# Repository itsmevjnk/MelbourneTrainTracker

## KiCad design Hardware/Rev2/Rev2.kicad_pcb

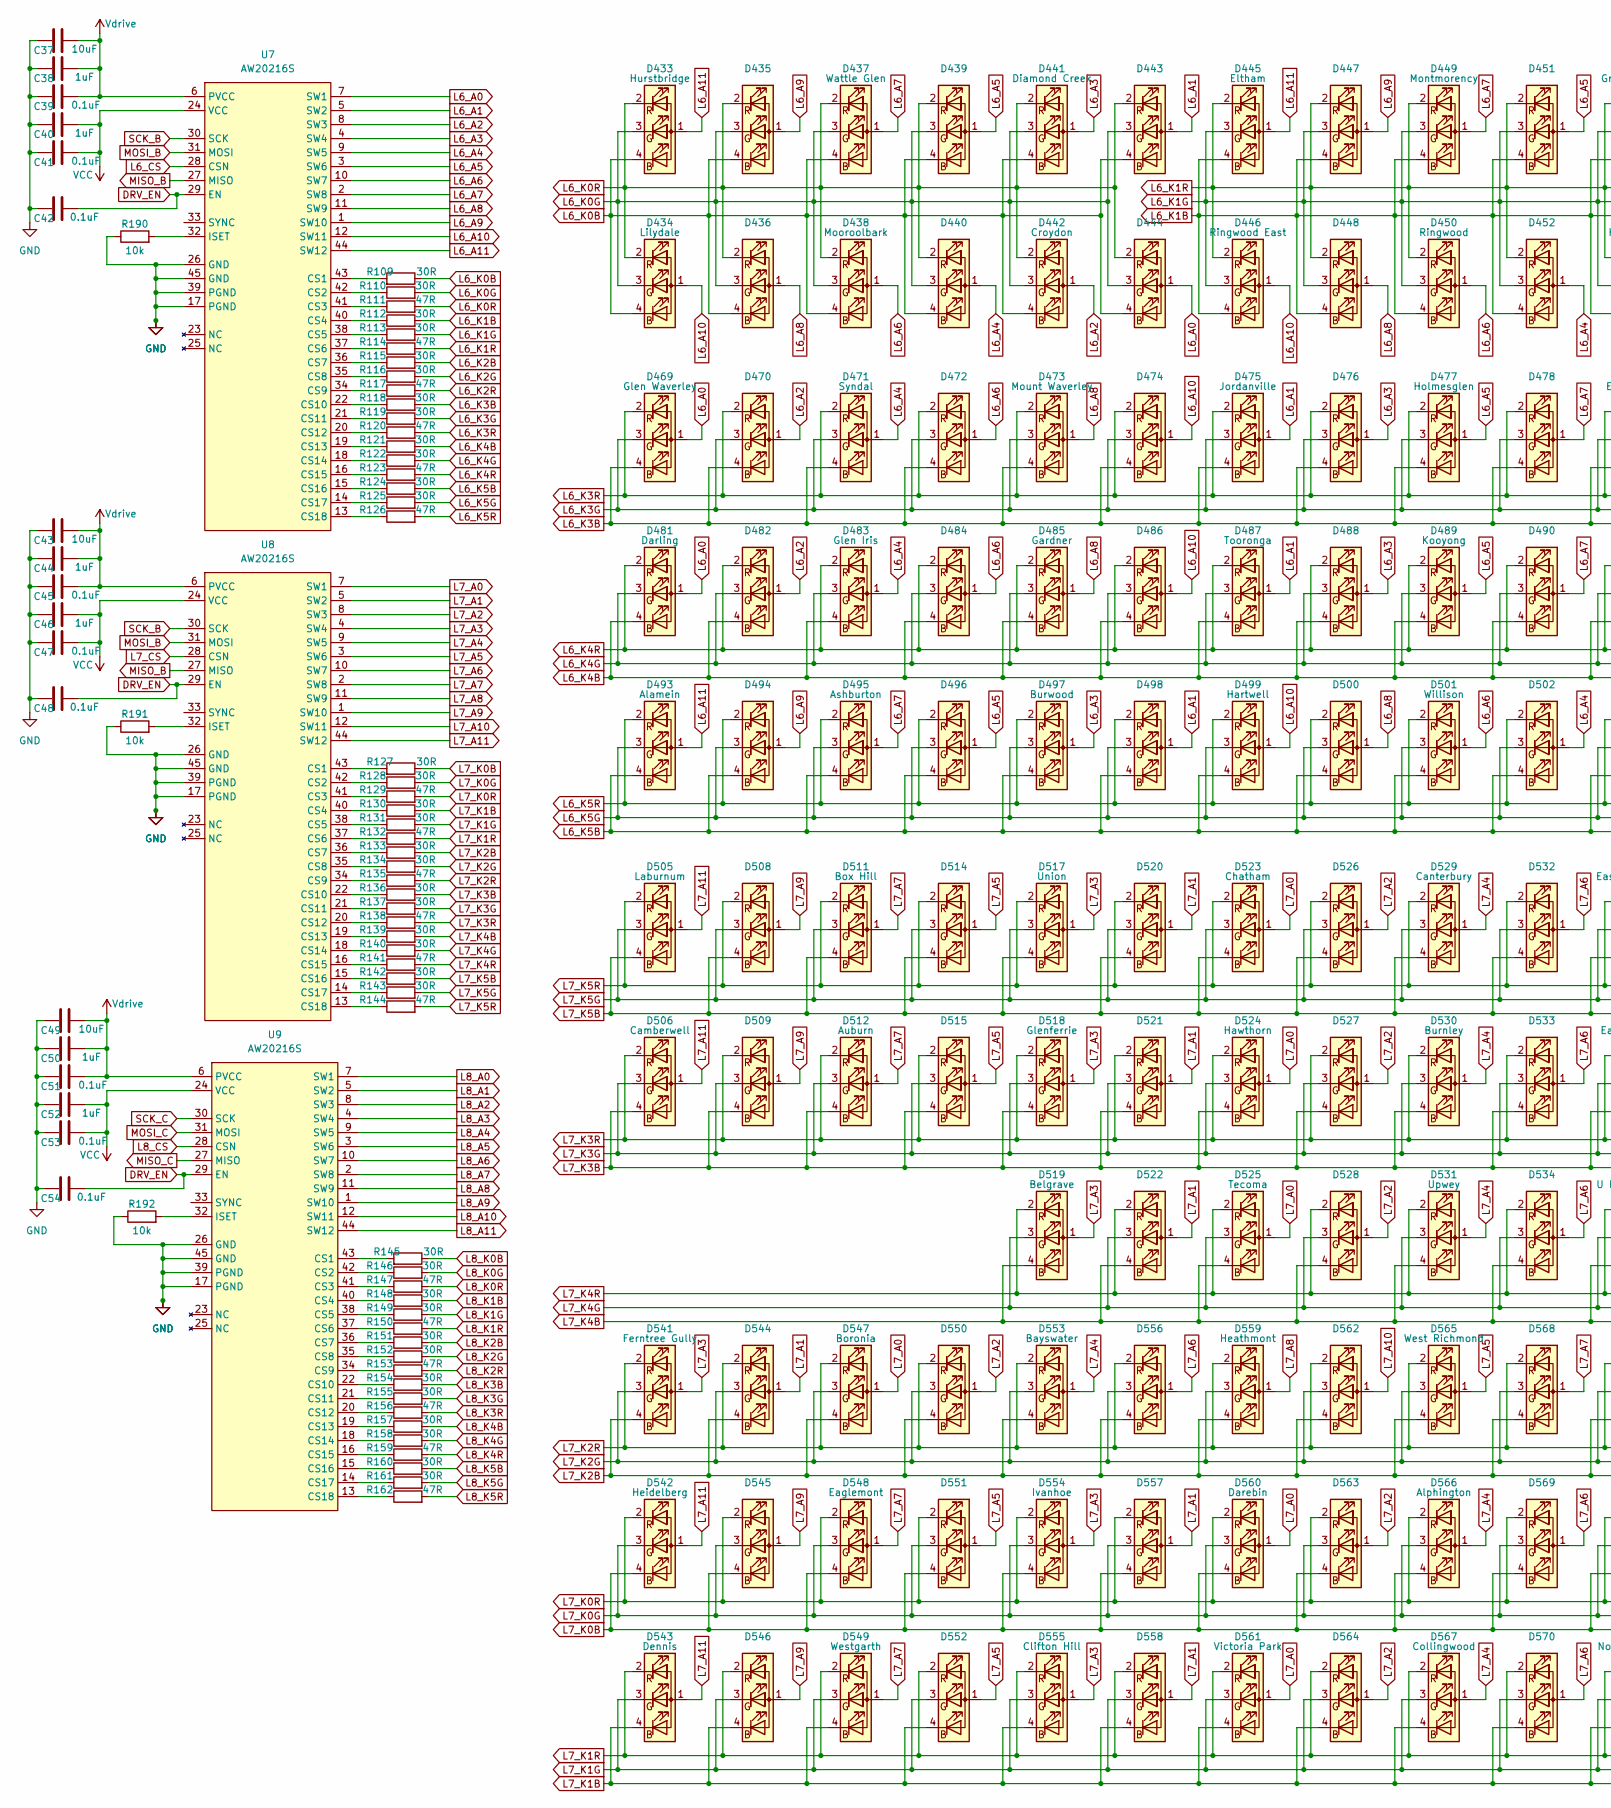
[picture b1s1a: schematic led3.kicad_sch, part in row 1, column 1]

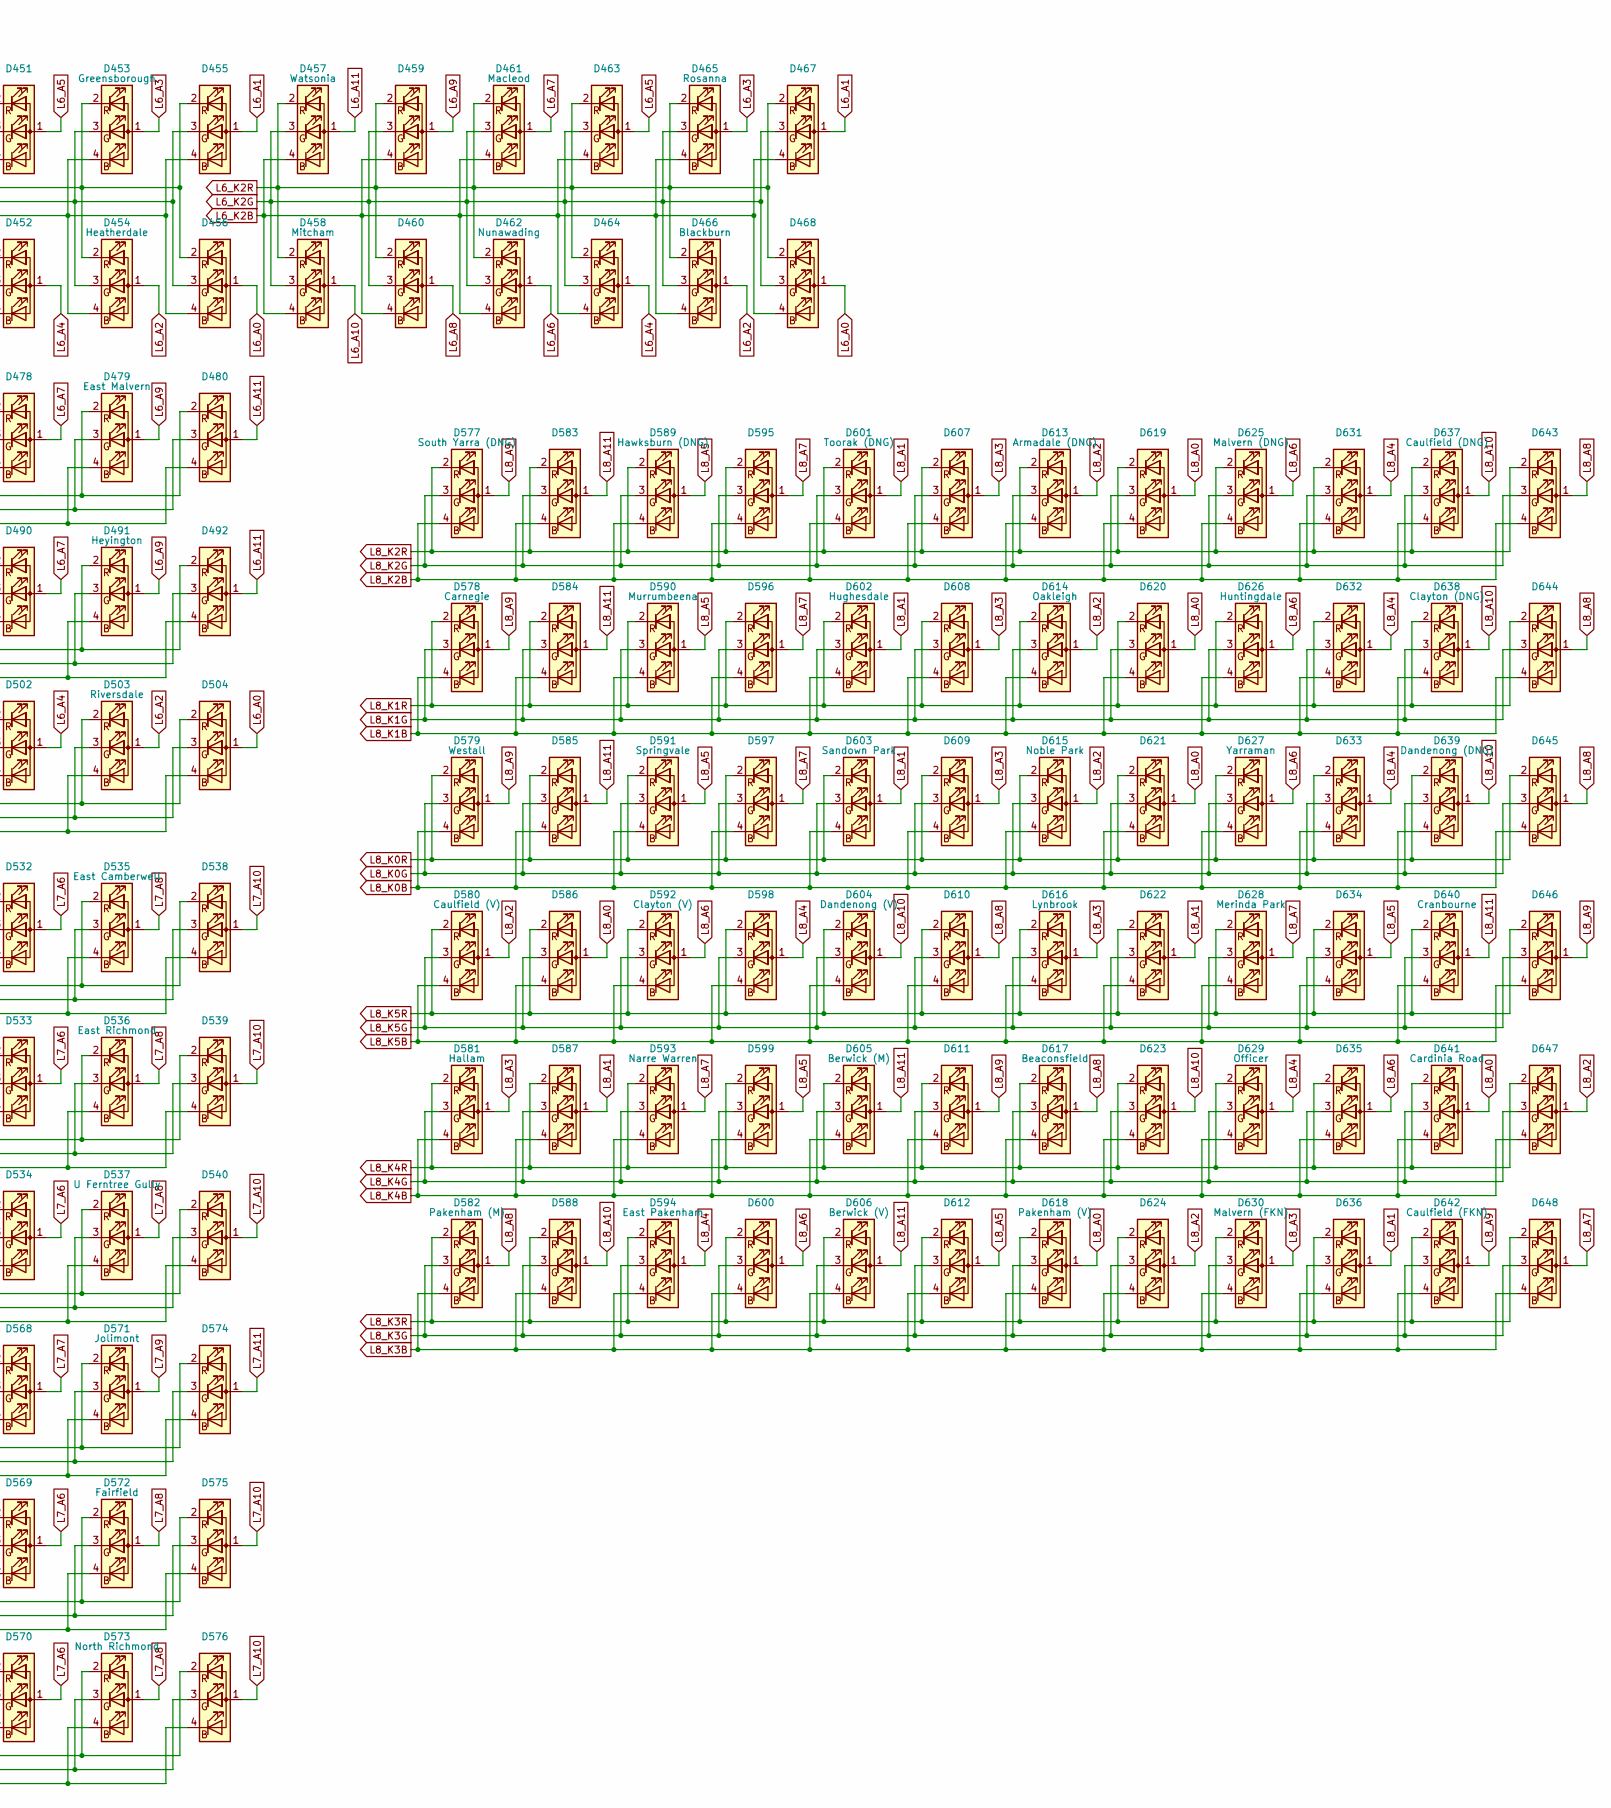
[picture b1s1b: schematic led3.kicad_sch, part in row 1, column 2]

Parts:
C37, C43, C49: 10uF; C_0805_2012Metric_Pad1.18x1.45mm_HandSolder; MPN C380332
C38, C40, C44, C46, C50, C52: 1uF; C_0603_1608Metric_Pad1.08x0.95mm_HandSolder; MPN C6119849
C39, C41, C42, C45, C47, C48, C51, C53, C54: 0.1uF; C_0603_1608Metric_Pad1.08x0.95mm_HandSolder; MPN C14663
D433, D434, D435, D436, D437, D438, D439, D440, D441, D442, D443, D444, D445, D446, D447, D448, D449, D450, D451, D452, D453, D454, D455, D456, D457, D458, D459, D460, D461, D462, D463, D464, D465, D466, D467, D468, D469, D470, D471, D472, D473, D474, D475, D476, D477, D478, D479, D480, D481, D482, D483, D484, D485, D486, D487, D488, D489, D490, D491, D492, D493, D494, D495, D496, D497, D498, D499, D500, D501, D502, D503, D504, D505, D506, D508, D509, D511, D512, D514, D515, D517, D518, D519, D520, D521, D522, D523, D524, D525, D526, D527, D528, D529, D530, D531, D532, D533, D534, D535, D536, D537, D538, D539, D540, D541, D542, D543, D544, D545, D546, D547, D548, D549, D550, D551, D552, D553, D554, D555, D556, D557, D558, D559, D560, D561, D562, D563, D564, D565, D566, D567, D568, D569, D570, D571, D572, D573, D574, D575, D576, D577, D578, D579, D580, D581, D582, D583, D584, D585, D586, D587, D588, D589, D590, D591, D592, D593, D594, D595, D596, D597, D598, D599, D600, D601, D602, D603, D604, D605, D606, D607, D608, D609, D610, D611, D612, D613, D614, D615, D616, D617, D618, D619, D620, D621, D622, D623, D624, D625, D626, D627, D628, D629, D630, D631, D632, D633, D634, D635, D636, D637, D638, D639, D640, D641, D642, D643, D644, D645, D646, D647, D648: XL-B1010RGBT-HF; LED_RGB_Xinglight-1010; MPN C22464515
R109, R110, R112, R113, R115, R116, R118, R119, R121, R122, R124, R125, R127, R128, R130, R131, R133, R134, R136, R137, R139, R140, R142, R143, R145, R146, R148, R149, R151, R152, R154, R155, R157, R158, R160, R161: 30R; R_0805_2012Metric_Pad1.20x1.40mm_HandSolder
R111, R114, R117, R120, R123, R126, R129, R132, R135, R138, R141, R144, R147, R150, R153, R156, R159, R162: 47R; R_0805_2012Metric_Pad1.20x1.40mm_HandSolder
R190, R191, R192: 10k; R_0603_1608Metric_Pad0.98x0.95mm_HandSolder; MPN C15401
U7, U8, U9: AW20216S; QFN-44-1EP_5x5mm_P0.4mm_EP2.45x2.45mm; MPN C7385556

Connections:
+3.3V: C40.2, C41.2, C46.2, C47.2, C52.2, C53.2, U7.24 (VCC), U8.24 (VCC), U9.24 (VCC); also elsewhere on the board
+5V: C37.2, C38.2, C39.2, C43.2, C44.2, C45.2, C49.2, C50.2, C51.2, U7.6 (PVCC), U8.6 (PVCC), U9.6 (PVCC); also elsewhere on the board
DRV_EN: C42.2, C48.2, C54.2, U7.29 (EN), U8.29 (EN), U9.29 (EN); also elsewhere on the board
GND: C37.1, C38.1, C39.1, C40.1, C41.1, C42.1, C43.1, C44.1, C45.1, C46.1, C47.1, C48.1, C49.1, C50.1, C51.1, C52.1, C53.1, C54.1, R190.1, R191.1, R192.1, U7.17 (PGND), U7.26 (GND), U7.39 (PGND), U7.45 (GND), U8.17 (PGND), U8.26 (GND), U8.39 (PGND), U8.45 (GND), U9.17 (PGND), U9.26 (GND), U9.39 (PGND), U9.45 (GND); also elsewhere on the board
L6_A0: D444.1 (A), D456.1 (A), D468.1 (A), D469.1 (A), D481.1 (A), D504.1 (A), U7.7 (SW1)
L6_A1: D443.1 (A), D455.1 (A), D467.1 (A), D475.1 (A), D487.1 (A), D498.1 (A), U7.5 (SW2)
L6_A2: D442.1 (A), D454.1 (A), D466.1 (A), D470.1 (A), D482.1 (A), D503.1 (A), U7.8 (SW3)
L6_A3: D441.1 (A), D453.1 (A), D465.1 (A), D476.1 (A), D488.1 (A), D497.1 (A), U7.4 (SW4)
L6_A4: D440.1 (A), D452.1 (A), D464.1 (A), D471.1 (A), D483.1 (A), D502.1 (A), U7.9 (SW5)
L6_A5: D439.1 (A), D451.1 (A), D463.1 (A), D477.1 (A), D489.1 (A), D496.1 (A), U7.3 (SW6)
L6_A6: D438.1 (A), D450.1 (A), D462.1 (A), D472.1 (A), D484.1 (A), D501.1 (A), U7.10 (SW7)
L6_A7: D437.1 (A), D449.1 (A), D461.1 (A), D478.1 (A), D490.1 (A), D495.1 (A), U7.2 (SW8)
L6_A8: D436.1 (A), D448.1 (A), D460.1 (A), D473.1 (A), D485.1 (A), D500.1 (A), U7.11 (SW9)
L6_A9: D435.1 (A), D447.1 (A), D459.1 (A), D479.1 (A), D491.1 (A), D494.1 (A), U7.1 (SW10)
L6_A10: D434.1 (A), D446.1 (A), D458.1 (A), D474.1 (A), D486.1 (A), D499.1 (A), U7.12 (SW11)
L6_A11: D433.1 (A), D445.1 (A), D457.1 (A), D480.1 (A), D492.1 (A), D493.1 (A), U7.44 (SW12)
L6_CS: U7.28 (CSN); also elsewhere on the board
L6_K0B: D433.4 (BK), D434.4 (BK), D435.4 (BK), D436.4 (BK), D437.4 (BK), D438.4 (BK), D439.4 (BK), D440.4 (BK), D441.4 (BK), D442.4 (BK), D443.4 (BK), D444.4 (BK), R109.1
L6_K0G: D433.3 (GK), D434.3 (GK), D435.3 (GK), D436.3 (GK), D437.3 (GK), D438.3 (GK), D439.3 (GK), D440.3 (GK), D441.3 (GK), D442.3 (GK), D443.3 (GK), D444.3 (GK), R110.2
L6_K0R: D433.2 (RK), D434.2 (RK), D435.2 (RK), D436.2 (RK), D437.2 (RK), D438.2 (RK), D439.2 (RK), D440.2 (RK), D441.2 (RK), D442.2 (RK), D443.2 (RK), D444.2 (RK), R111.2
L6_K1B: D445.4 (BK), D446.4 (BK), D447.4 (BK), D448.4 (BK), D449.4 (BK), D450.4 (BK), D451.4 (BK), D452.4 (BK), D453.4 (BK), D454.4 (BK), D455.4 (BK), D456.4 (BK), R112.2
L6_K1G: D445.3 (GK), D446.3 (GK), D447.3 (GK), D448.3 (GK), D449.3 (GK), D450.3 (GK), D451.3 (GK), D452.3 (GK), D453.3 (GK), D454.3 (GK), D455.3 (GK), D456.3 (GK), R113.2
L6_K1R: D445.2 (RK), D446.2 (RK), D447.2 (RK), D448.2 (RK), D449.2 (RK), D450.2 (RK), D451.2 (RK), D452.2 (RK), D453.2 (RK), D454.2 (RK), D455.2 (RK), D456.2 (RK), R114.2
L6_K2B: D457.4 (BK), D458.4 (BK), D459.4 (BK), D460.4 (BK), D461.4 (BK), D462.4 (BK), D463.4 (BK), D464.4 (BK), D465.4 (BK), D466.4 (BK), D467.4 (BK), D468.4 (BK), R115.2
L6_K2G: D457.3 (GK), D458.3 (GK), D459.3 (GK), D460.3 (GK), D461.3 (GK), D462.3 (GK), D463.3 (GK), D464.3 (GK), D465.3 (GK), D466.3 (GK), D467.3 (GK), D468.3 (GK), R116.2
L6_K2R: D457.2 (RK), D458.2 (RK), D459.2 (RK), D460.2 (RK), D461.2 (RK), D462.2 (RK), D463.2 (RK), D464.2 (RK), D465.2 (RK), D466.2 (RK), D467.2 (RK), D468.2 (RK), R117.2
L6_K3B: D469.4 (BK), D470.4 (BK), D471.4 (BK), D472.4 (BK), D473.4 (BK), D474.4 (BK), D475.4 (BK), D476.4 (BK), D477.4 (BK), D478.4 (BK), D479.4 (BK), D480.4 (BK), R118.2
L6_K3G: D469.3 (GK), D470.3 (GK), D471.3 (GK), D472.3 (GK), D473.3 (GK), D474.3 (GK), D475.3 (GK), D476.3 (GK), D477.3 (GK), D478.3 (GK), D479.3 (GK), D480.3 (GK), R119.2
L6_K3R: D469.2 (RK), D470.2 (RK), D471.2 (RK), D472.2 (RK), D473.2 (RK), D474.2 (RK), D475.2 (RK), D476.2 (RK), D477.2 (RK), D478.2 (RK), D479.2 (RK), D480.2 (RK), R120.2
L6_K4B: D481.4 (BK), D482.4 (BK), D483.4 (BK), D484.4 (BK), D485.4 (BK), D486.4 (BK), D487.4 (BK), D488.4 (BK), D489.4 (BK), D490.4 (BK), D491.4 (BK), D492.4 (BK), R121.2
L6_K4G: D481.3 (GK), D482.3 (GK), D483.3 (GK), D484.3 (GK), D485.3 (GK), D486.3 (GK), D487.3 (GK), D488.3 (GK), D489.3 (GK), D490.3 (GK), D491.3 (GK), D492.3 (GK), R122.2
L6_K4R: D481.2 (RK), D482.2 (RK), D483.2 (RK), D484.2 (RK), D485.2 (RK), D486.2 (RK), D487.2 (RK), D488.2 (RK), D489.2 (RK), D490.2 (RK), D491.2 (RK), D492.2 (RK), R123.2
L6_K5B: D493.4 (BK), D494.4 (BK), D495.4 (BK), D496.4 (BK), D497.4 (BK), D498.4 (BK), D499.4 (BK), D500.4 (BK), D501.4 (BK), D502.4 (BK), D503.4 (BK), D504.4 (BK), R124.2
L6_K5G: D493.3 (GK), D494.3 (GK), D495.3 (GK), D496.3 (GK), D497.3 (GK), D498.3 (GK), D499.3 (GK), D500.3 (GK), D501.3 (GK), D502.3 (GK), D503.3 (GK), D504.3 (GK), R125.2
L6_K5R: D493.2 (RK), D494.2 (RK), D495.2 (RK), D496.2 (RK), D497.2 (RK), D498.2 (RK), D499.2 (RK), D500.2 (RK), D501.2 (RK), D502.2 (RK), D503.2 (RK), D504.2 (RK), R126.2
L7_A0: D523.1 (A), D524.1 (A), D525.1 (A), D547.1 (A), D560.1 (A), D561.1 (A), U8.7 (SW1)
L7_A1: D520.1 (A), D521.1 (A), D522.1 (A), D544.1 (A), D557.1 (A), D558.1 (A), U8.5 (SW2)
L7_A2: D526.1 (A), D527.1 (A), D528.1 (A), D550.1 (A), D563.1 (A), D564.1 (A), U8.8 (SW3)
L7_A3: D517.1 (A), D518.1 (A), D519.1 (A), D541.1 (A), D554.1 (A), D555.1 (A), U8.4 (SW4)
L7_A4: D529.1 (A), D530.1 (A), D531.1 (A), D553.1 (A), D566.1 (A), D567.1 (A), U8.9 (SW5)
L7_A5: D514.1 (A), D515.1 (A), D551.1 (A), D552.1 (A), D565.1 (A), U8.3 (SW6)
L7_A6: D532.1 (A), D533.1 (A), D534.1 (A), D556.1 (A), D569.1 (A), D570.1 (A), U8.10 (SW7)
L7_A7: D511.1 (A), D512.1 (A), D548.1 (A), D549.1 (A), D568.1 (A), U8.2 (SW8)
L7_A8: D535.1 (A), D536.1 (A), D537.1 (A), D559.1 (A), D572.1 (A), D573.1 (A), U8.11 (SW9)
L7_A9: D508.1 (A), D509.1 (A), D545.1 (A), D546.1 (A), D571.1 (A), U8.1 (SW10)
L7_A10: D538.1 (A), D539.1 (A), D540.1 (A), D562.1 (A), D575.1 (A), D576.1 (A), U8.12 (SW11)
L7_A11: D505.1 (A), D506.1 (A), D542.1 (A), D543.1 (A), D574.1 (A), U8.44 (SW12)
L7_CS: U8.28 (CSN); also elsewhere on the board
L7_K0B: D542.4 (BK), D545.4 (BK), D548.4 (BK), D551.4 (BK), D554.4 (BK), D557.4 (BK), D560.4 (BK), D563.4 (BK), D566.4 (BK), D569.4 (BK), D572.4 (BK), D575.4 (BK), R127.1
L7_K0G: D542.3 (GK), D545.3 (GK), D548.3 (GK), D551.3 (GK), D554.3 (GK), D557.3 (GK), D560.3 (GK), D563.3 (GK), D566.3 (GK), D569.3 (GK), D572.3 (GK), D575.3 (GK), R128.2
L7_K0R: D542.2 (RK), D545.2 (RK), D548.2 (RK), D551.2 (RK), D554.2 (RK), D557.2 (RK), D560.2 (RK), D563.2 (RK), D566.2 (RK), D569.2 (RK), D572.2 (RK), D575.2 (RK), R129.2
L7_K1B: D543.4 (BK), D546.4 (BK), D549.4 (BK), D552.4 (BK), D555.4 (BK), D558.4 (BK), D561.4 (BK), D564.4 (BK), D567.4 (BK), D570.4 (BK), D573.4 (BK), D576.4 (BK), R130.2
L7_K1G: D543.3 (GK), D546.3 (GK), D549.3 (GK), D552.3 (GK), D555.3 (GK), D558.3 (GK), D561.3 (GK), D564.3 (GK), D567.3 (GK), D570.3 (GK), D573.3 (GK), D576.3 (GK), R131.2
L7_K1R: D543.2 (RK), D546.2 (RK), D549.2 (RK), D552.2 (RK), D555.2 (RK), D558.2 (RK), D561.2 (RK), D564.2 (RK), D567.2 (RK), D570.2 (RK), D573.2 (RK), D576.2 (RK), R132.2
L7_K2B: D541.4 (BK), D544.4 (BK), D547.4 (BK), D550.4 (BK), D553.4 (BK), D556.4 (BK), D559.4 (BK), D562.4 (BK), D565.4 (BK), D568.4 (BK), D571.4 (BK), D574.4 (BK), R133.2
L7_K2G: D541.3 (GK), D544.3 (GK), D547.3 (GK), D550.3 (GK), D553.3 (GK), D556.3 (GK), D559.3 (GK), D562.3 (GK), D565.3 (GK), D568.3 (GK), D571.3 (GK), D574.3 (GK), R134.2
L7_K2R: D541.2 (RK), D544.2 (RK), D547.2 (RK), D550.2 (RK), D553.2 (RK), D556.2 (RK), D559.2 (RK), D562.2 (RK), D565.2 (RK), D568.2 (RK), D571.2 (RK), D574.2 (RK), R135.2
L7_K3B: D506.4 (BK), D509.4 (BK), D512.4 (BK), D515.4 (BK), D518.4 (BK), D521.4 (BK), D524.4 (BK), D527.4 (BK), D530.4 (BK), D533.4 (BK), D536.4 (BK), D539.4 (BK), R136.2
L7_K3G: D506.3 (GK), D509.3 (GK), D512.3 (GK), D515.3 (GK), D518.3 (GK), D521.3 (GK), D524.3 (GK), D527.3 (GK), D530.3 (GK), D533.3 (GK), D536.3 (GK), D539.3 (GK), R137.2
L7_K3R: D506.2 (RK), D509.2 (RK), D512.2 (RK), D515.2 (RK), D518.2 (RK), D521.2 (RK), D524.2 (RK), D527.2 (RK), D530.2 (RK), D533.2 (RK), D536.2 (RK), D539.2 (RK), R138.2
L7_K4B: D519.4 (BK), D522.4 (BK), D525.4 (BK), D528.4 (BK), D531.4 (BK), D534.4 (BK), D537.4 (BK), D540.4 (BK), R139.2
L7_K4G: D519.3 (GK), D522.3 (GK), D525.3 (GK), D528.3 (GK), D531.3 (GK), D534.3 (GK), D537.3 (GK), D540.3 (GK), R140.2
L7_K4R: D519.2 (RK), D522.2 (RK), D525.2 (RK), D528.2 (RK), D531.2 (RK), D534.2 (RK), D537.2 (RK), D540.2 (RK), R141.2
L7_K5B: D505.4 (BK), D508.4 (BK), D511.4 (BK), D514.4 (BK), D517.4 (BK), D520.4 (BK), D523.4 (BK), D526.4 (BK), D529.4 (BK), D532.4 (BK), D535.4 (BK), D538.4 (BK), R142.2
L7_K5G: D505.3 (GK), D508.3 (GK), D511.3 (GK), D514.3 (GK), D517.3 (GK), D520.3 (GK), D523.3 (GK), D526.3 (GK), D529.3 (GK), D532.3 (GK), D535.3 (GK), D538.3 (GK), R143.2
L7_K5R: D505.2 (RK), D508.2 (RK), D511.2 (RK), D514.2 (RK), D517.2 (RK), D520.2 (RK), D523.2 (RK), D526.2 (RK), D529.2 (RK), D532.2 (RK), D535.2 (RK), D538.2 (RK), R144.2
L8_A0: D586.1 (A), D618.1 (A), D619.1 (A), D620.1 (A), D621.1 (A), D641.1 (A), U9.7 (SW1)
L8_A1: D587.1 (A), D601.1 (A), D602.1 (A), D603.1 (A), D622.1 (A), D636.1 (A), U9.5 (SW2)
L8_A2: D580.1 (A), D613.1 (A), D614.1 (A), D615.1 (A), D624.1 (A), D647.1 (A), U9.8 (SW3)
L8_A3: D581.1 (A), D607.1 (A), D608.1 (A), D609.1 (A), D616.1 (A), D630.1 (A), U9.4 (SW4)
L8_A4: D594.1 (A), D598.1 (A), D629.1 (A), D631.1 (A), D632.1 (A), D633.1 (A), U9.9 (SW5)
L8_A5: D589.1 (A), D590.1 (A), D591.1 (A), D599.1 (A), D612.1 (A), D634.1 (A), U9.3 (SW6)
L8_A6: D592.1 (A), D600.1 (A), D625.1 (A), D626.1 (A), D627.1 (A), D635.1 (A), U9.10 (SW7)
L8_A7: D593.1 (A), D595.1 (A), D596.1 (A), D597.1 (A), D628.1 (A), D648.1 (A), U9.2 (SW8)
L8_A8: D582.1 (A), D610.1 (A), D617.1 (A), D643.1 (A), D644.1 (A), D645.1 (A), U9.11 (SW9)
L8_A9: D577.1 (A), D578.1 (A), D579.1 (A), D611.1 (A), D642.1 (A), D646.1 (A), U9.1 (SW10)
L8_A10: D588.1 (A), D604.1 (A), D623.1 (A), D637.1 (A), D638.1 (A), D639.1 (A), U9.12 (SW11)
L8_A11: D583.1 (A), D584.1 (A), D585.1 (A), D605.1 (A), D606.1 (A), D640.1 (A), U9.44 (SW12)
L8_CS: U9.28 (CSN); also elsewhere on the board
L8_K0B: D579.4 (BK), D585.4 (BK), D591.4 (BK), D597.4 (BK), D603.4 (BK), D609.4 (BK), D615.4 (BK), D621.4 (BK), D627.4 (BK), D633.4 (BK), D639.4 (BK), D645.4 (BK), R145.1
L8_K0G: D579.3 (GK), D585.3 (GK), D591.3 (GK), D597.3 (GK), D603.3 (GK), D609.3 (GK), D615.3 (GK), D621.3 (GK), D627.3 (GK), D633.3 (GK), D639.3 (GK), D645.3 (GK), R146.2
L8_K0R: D579.2 (RK), D585.2 (RK), D591.2 (RK), D597.2 (RK), D603.2 (RK), D609.2 (RK), D615.2 (RK), D621.2 (RK), D627.2 (RK), D633.2 (RK), D639.2 (RK), D645.2 (RK), R147.2
L8_K1B: D578.4 (BK), D584.4 (BK), D590.4 (BK), D596.4 (BK), D602.4 (BK), D608.4 (BK), D614.4 (BK), D620.4 (BK), D626.4 (BK), D632.4 (BK), D638.4 (BK), D644.4 (BK), R148.2
L8_K1G: D578.3 (GK), D584.3 (GK), D590.3 (GK), D596.3 (GK), D602.3 (GK), D608.3 (GK), D614.3 (GK), D620.3 (GK), D626.3 (GK), D632.3 (GK), D638.3 (GK), D644.3 (GK), R149.2
L8_K1R: D578.2 (RK), D584.2 (RK), D590.2 (RK), D596.2 (RK), D602.2 (RK), D608.2 (RK), D614.2 (RK), D620.2 (RK), D626.2 (RK), D632.2 (RK), D638.2 (RK), D644.2 (RK), R150.2
L8_K2B: D577.4 (BK), D583.4 (BK), D589.4 (BK), D595.4 (BK), D601.4 (BK), D607.4 (BK), D613.4 (BK), D619.4 (BK), D625.4 (BK), D631.4 (BK), D637.4 (BK), D643.4 (BK), R151.2
L8_K2G: D577.3 (GK), D583.3 (GK), D589.3 (GK), D595.3 (GK), D601.3 (GK), D607.3 (GK), D613.3 (GK), D619.3 (GK), D625.3 (GK), D631.3 (GK), D637.3 (GK), D643.3 (GK), R152.2
L8_K2R: D577.2 (RK), D583.2 (RK), D589.2 (RK), D595.2 (RK), D601.2 (RK), D607.2 (RK), D613.2 (RK), D619.2 (RK), D625.2 (RK), D631.2 (RK), D637.2 (RK), D643.2 (RK), R153.2
L8_K3B: D582.4 (BK), D588.4 (BK), D594.4 (BK), D600.4 (BK), D606.4 (BK), D612.4 (BK), D618.4 (BK), D624.4 (BK), D630.4 (BK), D636.4 (BK), D642.4 (BK), D648.4 (BK), R154.2
L8_K3G: D582.3 (GK), D588.3 (GK), D594.3 (GK), D600.3 (GK), D606.3 (GK), D612.3 (GK), D618.3 (GK), D624.3 (GK), D630.3 (GK), D636.3 (GK), D642.3 (GK), D648.3 (GK), R155.2
L8_K3R: D582.2 (RK), D588.2 (RK), D594.2 (RK), D600.2 (RK), D606.2 (RK), D612.2 (RK), D618.2 (RK), D624.2 (RK), D630.2 (RK), D636.2 (RK), D642.2 (RK), D648.2 (RK), R156.2
L8_K4B: D581.4 (BK), D587.4 (BK), D593.4 (BK), D599.4 (BK), D605.4 (BK), D611.4 (BK), D617.4 (BK), D623.4 (BK), D629.4 (BK), D635.4 (BK), D641.4 (BK), D647.4 (BK), R157.2
L8_K4G: D581.3 (GK), D587.3 (GK), D593.3 (GK), D599.3 (GK), D605.3 (GK), D611.3 (GK), D617.3 (GK), D623.3 (GK), D629.3 (GK), D635.3 (GK), D641.3 (GK), D647.3 (GK), R158.2
L8_K4R: D581.2 (RK), D587.2 (RK), D593.2 (RK), D599.2 (RK), D605.2 (RK), D611.2 (RK), D617.2 (RK), D623.2 (RK), D629.2 (RK), D635.2 (RK), D641.2 (RK), D647.2 (RK), R159.2
L8_K5B: D580.4 (BK), D586.4 (BK), D592.4 (BK), D598.4 (BK), D604.4 (BK), D610.4 (BK), D616.4 (BK), D622.4 (BK), D628.4 (BK), D634.4 (BK), D640.4 (BK), D646.4 (BK), R160.2
L8_K5G: D580.3 (GK), D586.3 (GK), D592.3 (GK), D598.3 (GK), D604.3 (GK), D610.3 (GK), D616.3 (GK), D622.3 (GK), D628.3 (GK), D634.3 (GK), D640.3 (GK), D646.3 (GK), R161.2
L8_K5R: D580.2 (RK), D586.2 (RK), D592.2 (RK), D598.2 (RK), D604.2 (RK), D610.2 (RK), D616.2 (RK), D622.2 (RK), D628.2 (RK), D634.2 (RK), D640.2 (RK), D646.2 (RK), R162.2
MISO_B: U7.27 (MISO), U8.27 (MISO); also elsewhere on the board
MISO_C: U9.27 (MISO); also elsewhere on the board
MOSI_B: U7.31 (MOSI), U8.31 (MOSI); also elsewhere on the board
MOSI_C: U9.31 (MOSI); also elsewhere on the board
unnamed: R109.2, U7.43 (CS1)
unnamed: R110.1, U7.42 (CS2)
unnamed: R111.1, U7.41 (CS3)
unnamed: R112.1, U7.40 (CS4)
unnamed: R113.1, U7.38 (CS5)
unnamed: R114.1, U7.37 (CS6)
unnamed: R115.1, U7.36 (CS7)
unnamed: R116.1, U7.35 (CS8)
unnamed: R117.1, U7.34 (CS9)
unnamed: R118.1, U7.22 (CS10)
unnamed: R119.1, U7.21 (CS11)
unnamed: R120.1, U7.20 (CS12)
unnamed: R121.1, U7.19 (CS13)
unnamed: R122.1, U7.18 (CS14)
unnamed: R123.1, U7.16 (CS15)
unnamed: R124.1, U7.15 (CS16)
unnamed: R125.1, U7.14 (CS17)
unnamed: R126.1, U7.13 (CS18)
unnamed: R190.2, U7.32 (ISET)
unnamed: R127.2, U8.43 (CS1)
unnamed: R128.1, U8.42 (CS2)
unnamed: R129.1, U8.41 (CS3)
unnamed: R130.1, U8.40 (CS4)
unnamed: R131.1, U8.38 (CS5)
unnamed: R132.1, U8.37 (CS6)
unnamed: R133.1, U8.36 (CS7)
unnamed: R134.1, U8.35 (CS8)
unnamed: R135.1, U8.34 (CS9)
unnamed: R136.1, U8.22 (CS10)
unnamed: R137.1, U8.21 (CS11)
unnamed: R138.1, U8.20 (CS12)
unnamed: R139.1, U8.19 (CS13)
unnamed: R140.1, U8.18 (CS14)
unnamed: R141.1, U8.16 (CS15)
unnamed: R142.1, U8.15 (CS16)
unnamed: R143.1, U8.14 (CS17)
unnamed: R144.1, U8.13 (CS18)
unnamed: R191.2, U8.32 (ISET)
unnamed: R145.2, U9.43 (CS1)
unnamed: R146.1, U9.42 (CS2)
unnamed: R147.1, U9.41 (CS3)
unnamed: R148.1, U9.40 (CS4)
unnamed: R149.1, U9.38 (CS5)
unnamed: R150.1, U9.37 (CS6)
unnamed: R151.1, U9.36 (CS7)
unnamed: R152.1, U9.35 (CS8)
unnamed: R153.1, U9.34 (CS9)
unnamed: R154.1, U9.22 (CS10)
unnamed: R155.1, U9.21 (CS11)
unnamed: R156.1, U9.20 (CS12)
unnamed: R157.1, U9.19 (CS13)
unnamed: R158.1, U9.18 (CS14)
unnamed: R159.1, U9.16 (CS15)
unnamed: R160.1, U9.15 (CS16)
unnamed: R161.1, U9.14 (CS17)
unnamed: R162.1, U9.13 (CS18)
unnamed: R192.2, U9.32 (ISET)
SCK_B: U7.30 (SCK), U8.30 (SCK); also elsewhere on the board
SCK_C: U9.30 (SCK); also elsewhere on the board

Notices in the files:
Hardware/Rev2/Rev2.kicad_pcb:
Transport Pictograms, GTFS Schedule and GTFS Realtime API by the
Department of Transport and Planning are licensed under CC BY 4.0.
